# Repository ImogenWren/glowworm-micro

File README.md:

# glowworm-micro

Project to build a small battery powered handheld lighting controller for creative macro photography

## Project Due Data: 25/12/25

## Desired Features
- Arduino IoT33 Controller (could be ported to ESP32)
- 1S Lipo battery pack with charger
- Power on and off device using external interrupts
- Rotary Encoder for changing values

- Buttons to select parameter
- Detachable WS2821 Led Strip with 3D printed diffuser options
- 3D printed & ergonomic case
- fastLED library

- 2 Channel Lighting, each channel will have independent
    - Hue
    - Saturation
    - Brightness

Additional control ->  blend mode
- Unblended -> Colours remain seperate
- Direct Blend ->  blend will mix colours directly  
- Colour wheel short blend -> two channels will blend via the shortest route around the colour wheel between them
- colour wheel long blend -> two channels will blend via the longest path around the colour wheel

## Strech Goals
- Save & Recall current settings on shutdown/powerup
- OLED screen displaying all parameters
- highlight currently selected parameter
- Battery indicator
- PCB for control system
- PCB for LED Strip
- Advanced colour palettes

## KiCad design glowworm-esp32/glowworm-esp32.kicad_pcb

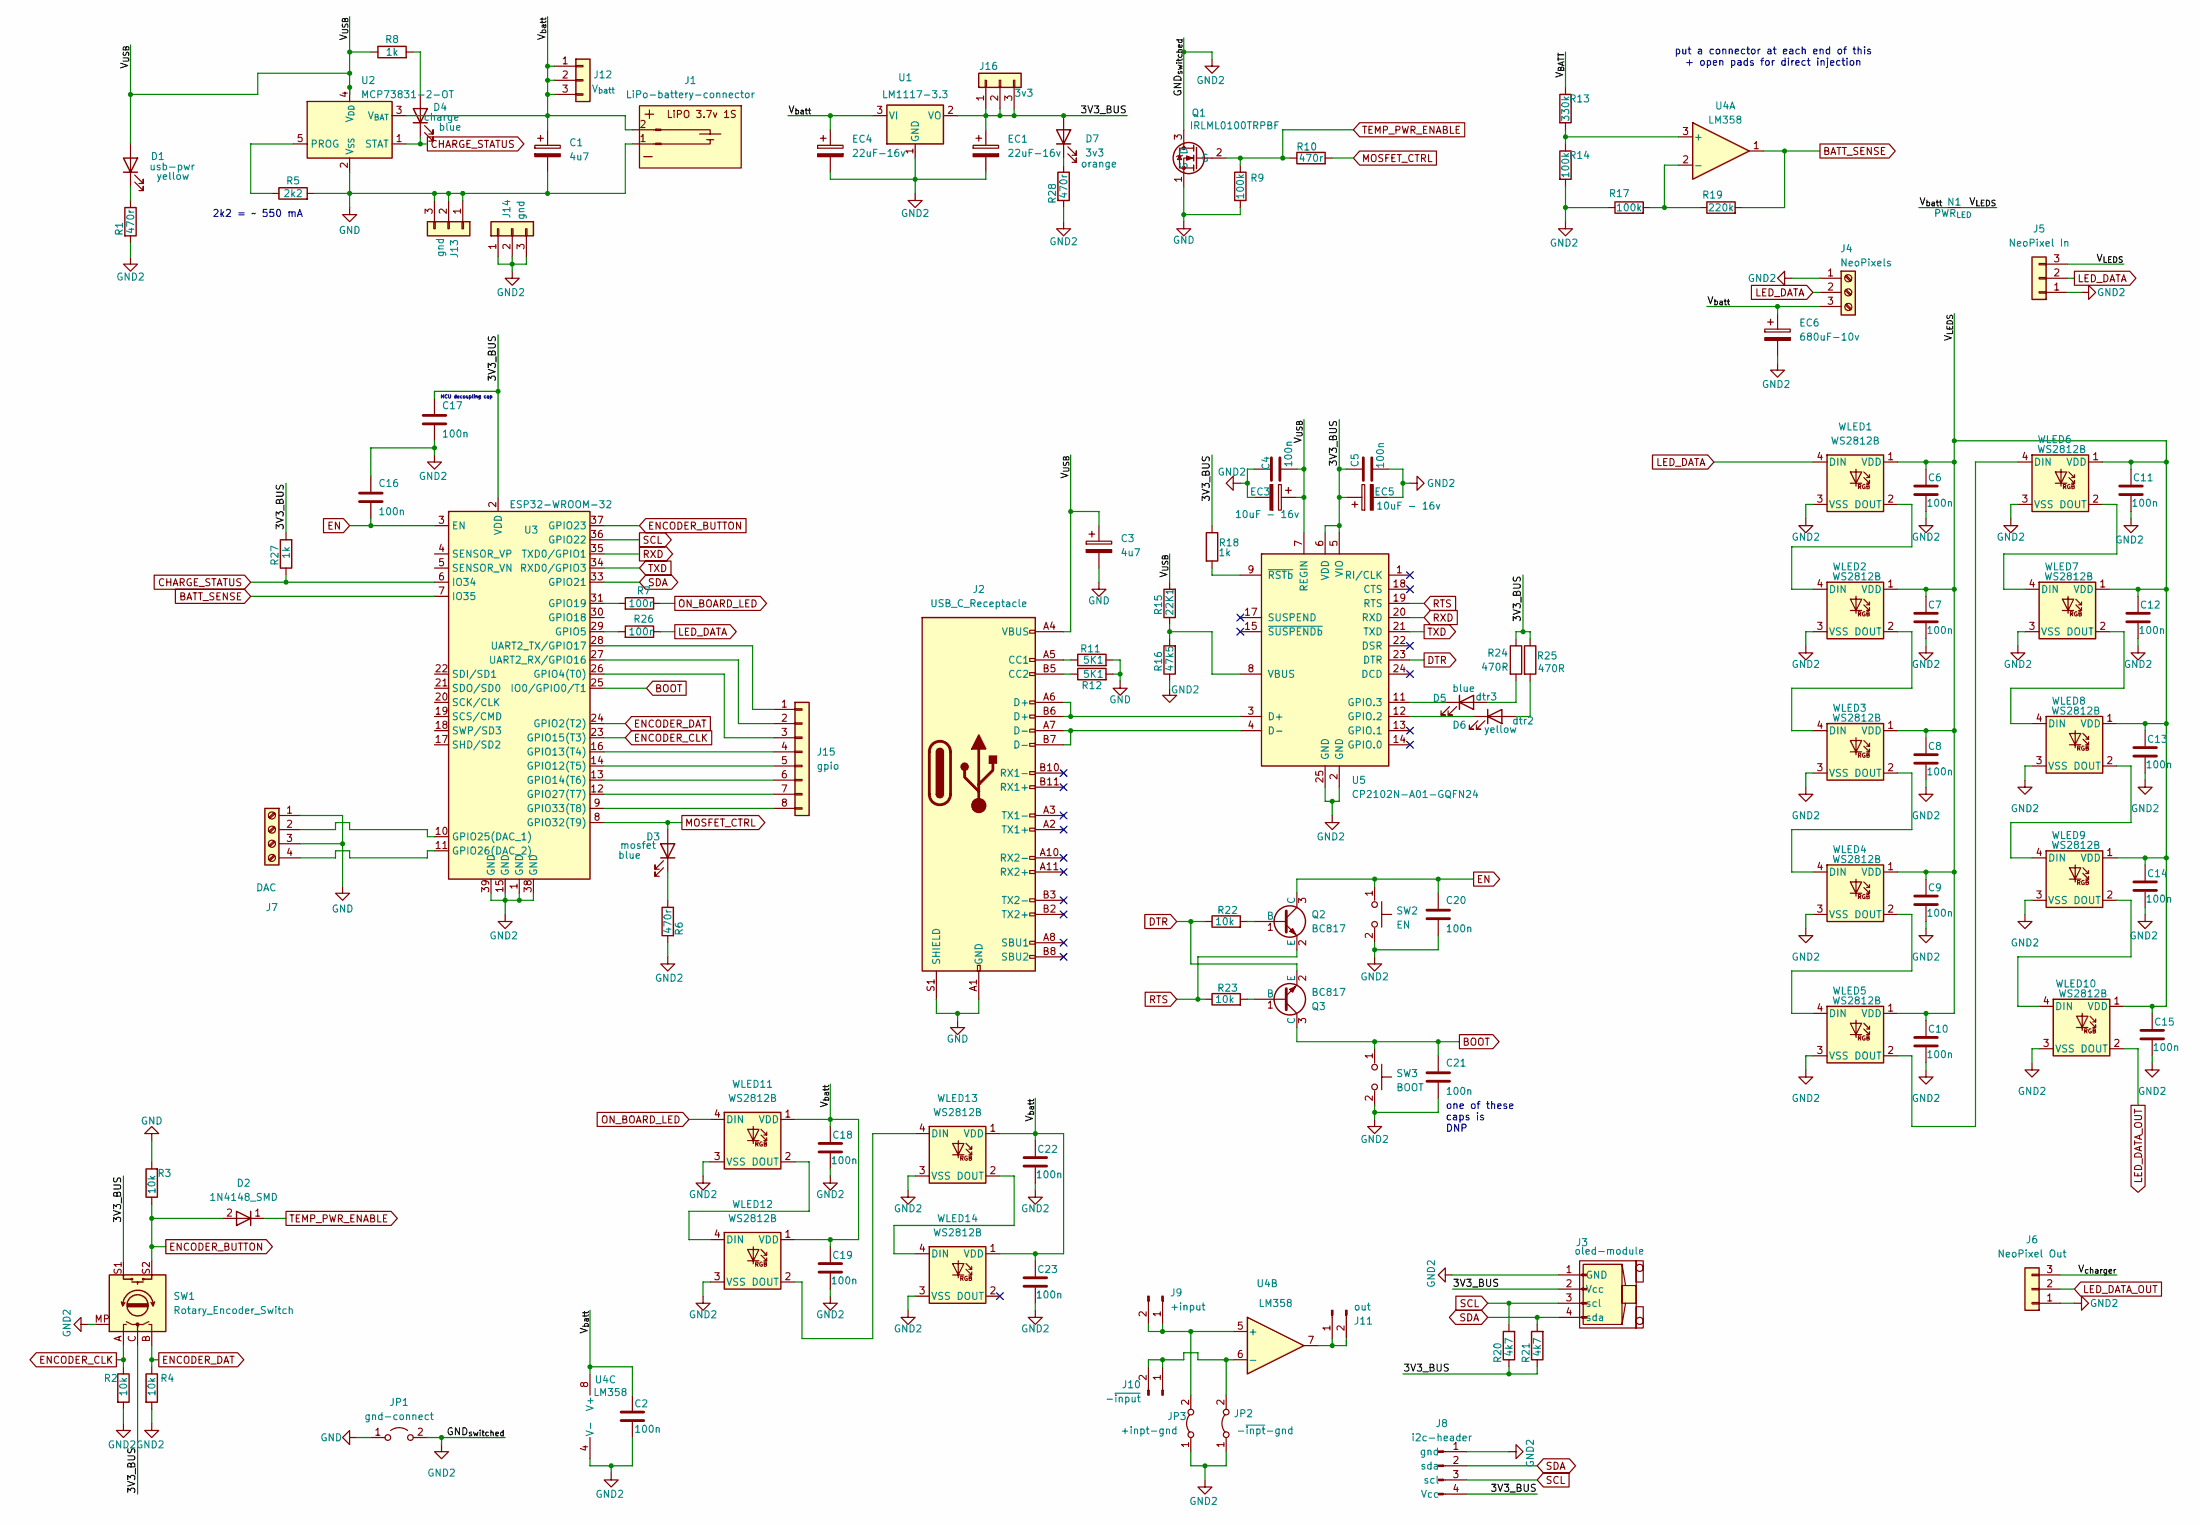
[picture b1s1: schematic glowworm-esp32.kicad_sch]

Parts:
C1, C3: 4u7; CP_EIA-2012-12_Kemet-R_Pad1.30x1.05mm_HandSolder; JLCpart C1954175
C2, C4, C5, C6, C7, C8, C9, C10, C11, C12, C13, C14, C15, C16, C17, C18, C19, C20, C21, C22, C23: 100n; C_0603_1608Metric_Pad1.08x0.95mm_HandSolder; JLCpart C779975
D1: usb-pwr; D_0603_1608Metric_Pad1.05x0.95mm_HandSolder; JLCpart C84261
D2: 1N4148_SMD; D_MiniMELF_kawaii
D3: mosfet; D_0603_1608Metric_Pad1.05x0.95mm_HandSolder; JLCpart C84259
D4: charge; D_0603_1608Metric_Pad1.05x0.95mm_HandSolder; JLCpart C84259
D5: dtr3; D_0603_1608Metric_Pad1.05x0.95mm_HandSolder; JLCpart C84259
D6: dtr2; D_0603_1608Metric_Pad1.05x0.95mm_HandSolder; JLCpart C84261
D7: 3v3; D_0805_2012Metric_Pad1.15x1.40mm_HandSolder
EC1, EC4: 22uF-16v; CP_Elec_4x5.4; JLCpart C3356
EC3, EC5: 10uF - 16v; CP_Elec_4x5.4; JLCpart C3357
EC6: 680uF-10v; CP_Elec_10x10; JLCpart C225872
J1: LiPo-battery-connector; Molex_KK-254_AE-6410-02A_1x02_P2.54mm_Vertical_copy
J2: USB_C_Receptacle; USB_C_Receptacle_GCT_USB4105-xx-A_16P_TopMnt_Horizontal; JLCpart C134092
J3: oled-module; oled-screen-i2c
J4: NeoPixels; TerminalBlock_01_03_medium_5.008mm
J5: NeoPixel In; PinHeader_1x03_P2.54mm_Vertical
J6: NeoPixel Out; PinHeader_1x03_P2.54mm_Vertical
J7: DAC; TerminalBlock_Phoenix_MPT-0,5-4-2.54_1x04_P2.54mm_Horizontal
J8: i2c-header; i2c-pin-header-A
J9: +input; PinHeader_1x02_P2.54mm_Vertical
J10: -~{input}; PinHeader_1x02_P2.54mm_Vertical
J11: out; PinHeader_1x02_P2.54mm_Vertical
J12: V_{batt}; PinHeader_1x03_P2.54mm_Vertical
J13, J14: gnd; PinHeader_1x03_P2.54mm_Vertical
J15: gpio; PinHeader_1x08_P2.54mm_Vertical
J16: 3v3; PinHeader_1x03_P2.54mm_Vertical
JP1: gnd-connect; SolderJumper-2_P1.3mm_Open_RoundedPad1.0x1.5mm
JP2: -~{inpt}-gnd; SolderJumper-2_P1.3mm_Bridged_RoundedPad1.0x1.5mm
JP3: +inpt-gnd; SolderJumper-2_P1.3mm_Bridged_RoundedPad1.0x1.5mm
N1: PWR_{LED}; NetTie-2_SMD_Pad0.5mm
Q1: IRLML0100TRPBF; SOT-23
Q2, Q3: BC817; SOT-23; JLCpart C2137
R1, R6, R10, R28: 470r; R_0603_1608Metric_Pad0.98x0.95mm_HandSolder
R2, R3, R4, R22, R23: 10k; R_0603_1608Metric_Pad0.98x0.95mm_HandSolder
R5: 2k2; R_0603_1608Metric_Pad0.98x0.95mm_HandSolder
R7, R26: 100r; R_0603_1608Metric_Pad0.98x0.95mm_HandSolder
R8, R18, R27: 1k; R_0603_1608Metric_Pad0.98x0.95mm_HandSolder
R9, R14, R17: 100k; R_0603_1608Metric_Pad0.98x0.95mm_HandSolder
R11, R12: 5K1; R_0603_1608Metric_Pad0.98x0.95mm_HandSolder
R13: 330k; R_0603_1608Metric_Pad0.98x0.95mm_HandSolder
R15: 22K1; R_0603_1608Metric_Pad0.98x0.95mm_HandSolder
R16: 47k5; R_0603_1608Metric_Pad0.98x0.95mm_HandSolder
R19: 220k; R_0603_1608Metric_Pad0.98x0.95mm_HandSolder
R20, R21: 4k7; R_0603_1608Metric_Pad0.98x0.95mm_HandSolder
R24, R25: 470R; R_0603_1608Metric_Pad0.98x0.95mm_HandSolder
SW1: Rotary_Encoder_Switch; RotaryEncoder_Alps_EC12E-Switch_Vertical_H20mm
SW2: EN; SW_SPST_EVQPE1; JLCpart C699451
SW3: BOOT; SW_SPST_EVQPE1; JLCpart C699451
U1: LM1117-3.3; SOT-223-3_TabPin2_1
U2: MCP73831-2-OT; SOT-23-5; JLCpart C424093
U3: ESP32-WROOM-32; JLCpart C473012 - C529577
U4: LM358; SOIC-8_3.9x4.9mm_P1.27mm
U5: CP2102N-A01-GQFN24; QFN-24-1EP_4x4mm_P0.5mm_EP2.6x2.6mm
WLED1, WLED2, WLED3, WLED4, WLED5, WLED6, WLED7, WLED8, WLED9, WLED10, WLED11, WLED12, WLED13, WLED14: WS2812B; LED_WS2812B_PLCC4_5.0x5.0mm_P3.2mm; JLCpart C2920042

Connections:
/3V3_BUS: C5.1, C17.1, D7.2 (A), EC1.1, EC5.1, J3.2 (Vcc), J8.4 (Vcc), J16.1, J16.2, J16.3, R18.1, R20.1, R21.1, R24.1, R25.1, R27.2, SW1.C, SW1.S1, U1.2 (VO), U3.2 (VDD), U5.5 (VIO), U5.6 (VDD)
/V_{BATT}: R13.1
/V_{LEDS}: C6.1, C7.1, C8.1, C9.1, C10.1, C11.1, C12.1, C13.1, C14.1, C15.1, J5.3, N1.2 (C), WLED1.1 (VDD), WLED2.1 (VDD), WLED3.1 (VDD), WLED4.1 (VDD), WLED5.1 (VDD), WLED6.1 (VDD), WLED7.1 (VDD), WLED8.1 (VDD), WLED9.1 (VDD), WLED10.1 (VDD)
/V_{USB}: C3.1, C4.2, D1.2 (A), EC3.1, J2.A4 (VBUS), J2.A9 (VBUS), J2.B4 (VBUS), J2.B9 (VBUS), R8.1, R15.2, U2.4 (V_{DD}), U5.7 (REGIN)
/V_{batt}: C1.1, C2.1, C18.1, C19.1, C22.1, C23.1, EC4.1, EC6.1, J1.2, J4.3 (Pin_1), J12.1, J12.2, J12.3, N1.1 (A), U1.3 (VI), U2.3 (V_{BAT}), U4.8 (V+), WLED11.1 (VDD), WLED12.1 (VDD), WLED13.1 (VDD), WLED14.1 (VDD)
/V_{charger}: J6.3
BATT_SENSE: R19.2, U3.7 (IO35), U4.1
BOOT: C21.1, Q3.3 (C), SW3.1, U3.25 (IO0/GPIO0/T1)
CHARGE_STATUS: D4.1 (K), R27.1, U2.1 (STAT), U3.6 (IO34)
DTR: Q3.2 (E), R22.1, U5.23 (DTR)
EN: C16.2, C20.1, Q2.3 (C), SW2.1, U3.3 (EN)
ENCODER_BUTTON: D2.2 (A), R3.1, SW1.S2, U3.37 (GPIO23)
ENCODER_CLK: R2.1, SW1.A, U3.23 (GPIO15(T3))
ENCODER_DAT: R4.1, SW1.B, U3.24 (GPIO2(T2))
GND: C1.2, C3.2, J1.1, J2.A1 (GND), J2.A12 (GND), J2.B1 (GND), J2.B12 (GND), J2.S1 (SHIELD), J7.1, J7.3, J13.1, J13.2, J13.3, JP1.1 (A), Q1.1 (S), R3.2, R5.2, R9.2, R11.2, R12.2, U2.2 (V_{SS})
GND2: C2.2, C4.1, C5.2, C6.2, C7.2, C8.2, C9.2, C10.2, C11.2, C12.2, C13.2, C14.2, C15.2, C16.1, C17.2, C18.2, C19.2, C20.2, C21.2, C22.2, C23.2, EC1.2, EC3.2, EC4.2, EC5.2, EC6.2, J3.1 (GND), J4.1, J5.1, J6.1, J8.1 (gnd), J14.1, J14.2, J14.3, JP1.2 (B), JP2.1 (A), JP3.1 (A), Q1.3 (D), R1.2, R2.2, R4.2, R6.2, R14.2, R16.1, R17.1, R28.2, SW1.MP, SW2.2, SW3.2, U1.1 (GND), U3.1 (GND), U3.15 (GND), U3.38 (GND), U3.39 (GND), U4.4 (V-), U5.2 (GND), U5.25 (GND), WLED1.3 (VSS), WLED2.3 (VSS), WLED3.3 (VSS), WLED4.3 (VSS), WLED5.3 (VSS), WLED6.3 (VSS), WLED7.3 (VSS), WLED8.3 (VSS), WLED9.3 (VSS), WLED10.3 (VSS), WLED11.3 (VSS), WLED12.3 (VSS), WLED13.3 (VSS), WLED14.3 (VSS)
LED_DATA: J4.2, J5.2, R26.1, WLED1.4 (DIN)
LED_DATA_OUT: J6.2, WLED10.2 (DOUT)
MOSFET_CTRL: D3.2 (A), R10.2, U3.8 (GPIO32(T9))
unnamed: D1.1 (K), R1.1
unnamed: D3.1 (K), R6.1
unnamed: D4.2 (A), R8.2
unnamed: D5.2 (A), R24.2
unnamed: D5.1 (K), U5.11 (GPIO.3)
unnamed: D6.2 (A), R25.2
unnamed: D6.1 (K), U5.12 (GPIO.2)
unnamed: D7.1 (K), R28.1
unnamed: J2.A5 (CC1), R11.1
unnamed: J2.B5 (CC2), R12.1
unnamed: J7.2, U3.10 (GPIO25(DAC_1))
unnamed: J7.4, U3.11 (GPIO26(DAC_2))
unnamed: J9.1, J9.2, JP3.2 (B), U4.5 (+)
unnamed: J10.1, J10.2, JP2.2 (B), U4.6 (-)
unnamed: J11.1, J11.2, U4.7
unnamed: J15.1, U3.28 (UART2_TX/GPIO17)
unnamed: J15.2, U3.27 (UART2_RX/GPIO16)
unnamed: J15.3, U3.26 (GPIO4(T0))
unnamed: J15.4, U3.16 (GPIO13(T4))
unnamed: J15.5, U3.14 (GPIO12(T5))
unnamed: J15.6, U3.13 (GPIO14(T6))
unnamed: J15.7, U3.12 (GPIO27(T7))
unnamed: J15.8, U3.9 (GPIO33(T8))
unnamed: Q2.1 (B), R22.2
unnamed: Q3.1 (B), R23.2
unnamed: R5.1, U2.5 (PROG)
unnamed: R26.2, U3.29 (GPIO5)
unnamed: R7.2, U3.31 (GPIO19)
unnamed: R13.2, R14.1, U4.3 (+)
unnamed: R17.2, R19.1, U4.2 (-)
unnamed: J2.A6 (D+), J2.B6 (D+), U5.3 (D+)
unnamed: J2.A7 (D-), J2.B7 (D-), U5.4 (D-)
unnamed: R15.1, R16.2, U5.8 (VBUS)
unnamed: R18.2, U5.9 (~RSTb)
unnamed: WLED1.2 (DOUT), WLED2.4 (DIN)
unnamed: WLED2.2 (DOUT), WLED3.4 (DIN)
unnamed: WLED3.2 (DOUT), WLED4.4 (DIN)
unnamed: WLED4.2 (DOUT), WLED5.4 (DIN)
unnamed: WLED5.2 (DOUT), WLED6.4 (DIN)
unnamed: WLED6.2 (DOUT), WLED7.4 (DIN)
unnamed: WLED7.2 (DOUT), WLED8.4 (DIN)
unnamed: WLED8.2 (DOUT), WLED9.4 (DIN)
unnamed: WLED9.2 (DOUT), WLED10.4 (DIN)
unnamed: WLED11.2 (DOUT), WLED12.4 (DIN)
unnamed: WLED12.2 (DOUT), WLED13.4 (DIN)
unnamed: WLED13.2 (DOUT), WLED14.4 (DIN)
ON_BOARD_LED: R7.1, WLED11.4 (DIN)
RTS: Q2.2 (E), R23.1, U5.19 (RTS)
RXD: U3.35 (TXD0/GPIO1), U5.20 (RXD)
SCL: J3.3 (scl), J8.3 (scl), R20.2, U3.36 (GPIO22)
SDA: J3.4 (sda), J8.2 (sda), R21.2, U3.33 (GPIO21)
TEMP_PWR_ENABLE: D2.1 (K), Q1.2 (G), R9.1, R10.1
TXD: U3.34 (RXD0/GPIO3), U5.21 (TXD)

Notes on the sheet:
put a connector at each end of this + open pads for direct injection
MCU decoupling cap
one of these caps is DNP
2k2 = ~ 550 mA

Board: 2 copper layers, 108 parts (0 on the bottom side), 70 nets, no tracks yet.

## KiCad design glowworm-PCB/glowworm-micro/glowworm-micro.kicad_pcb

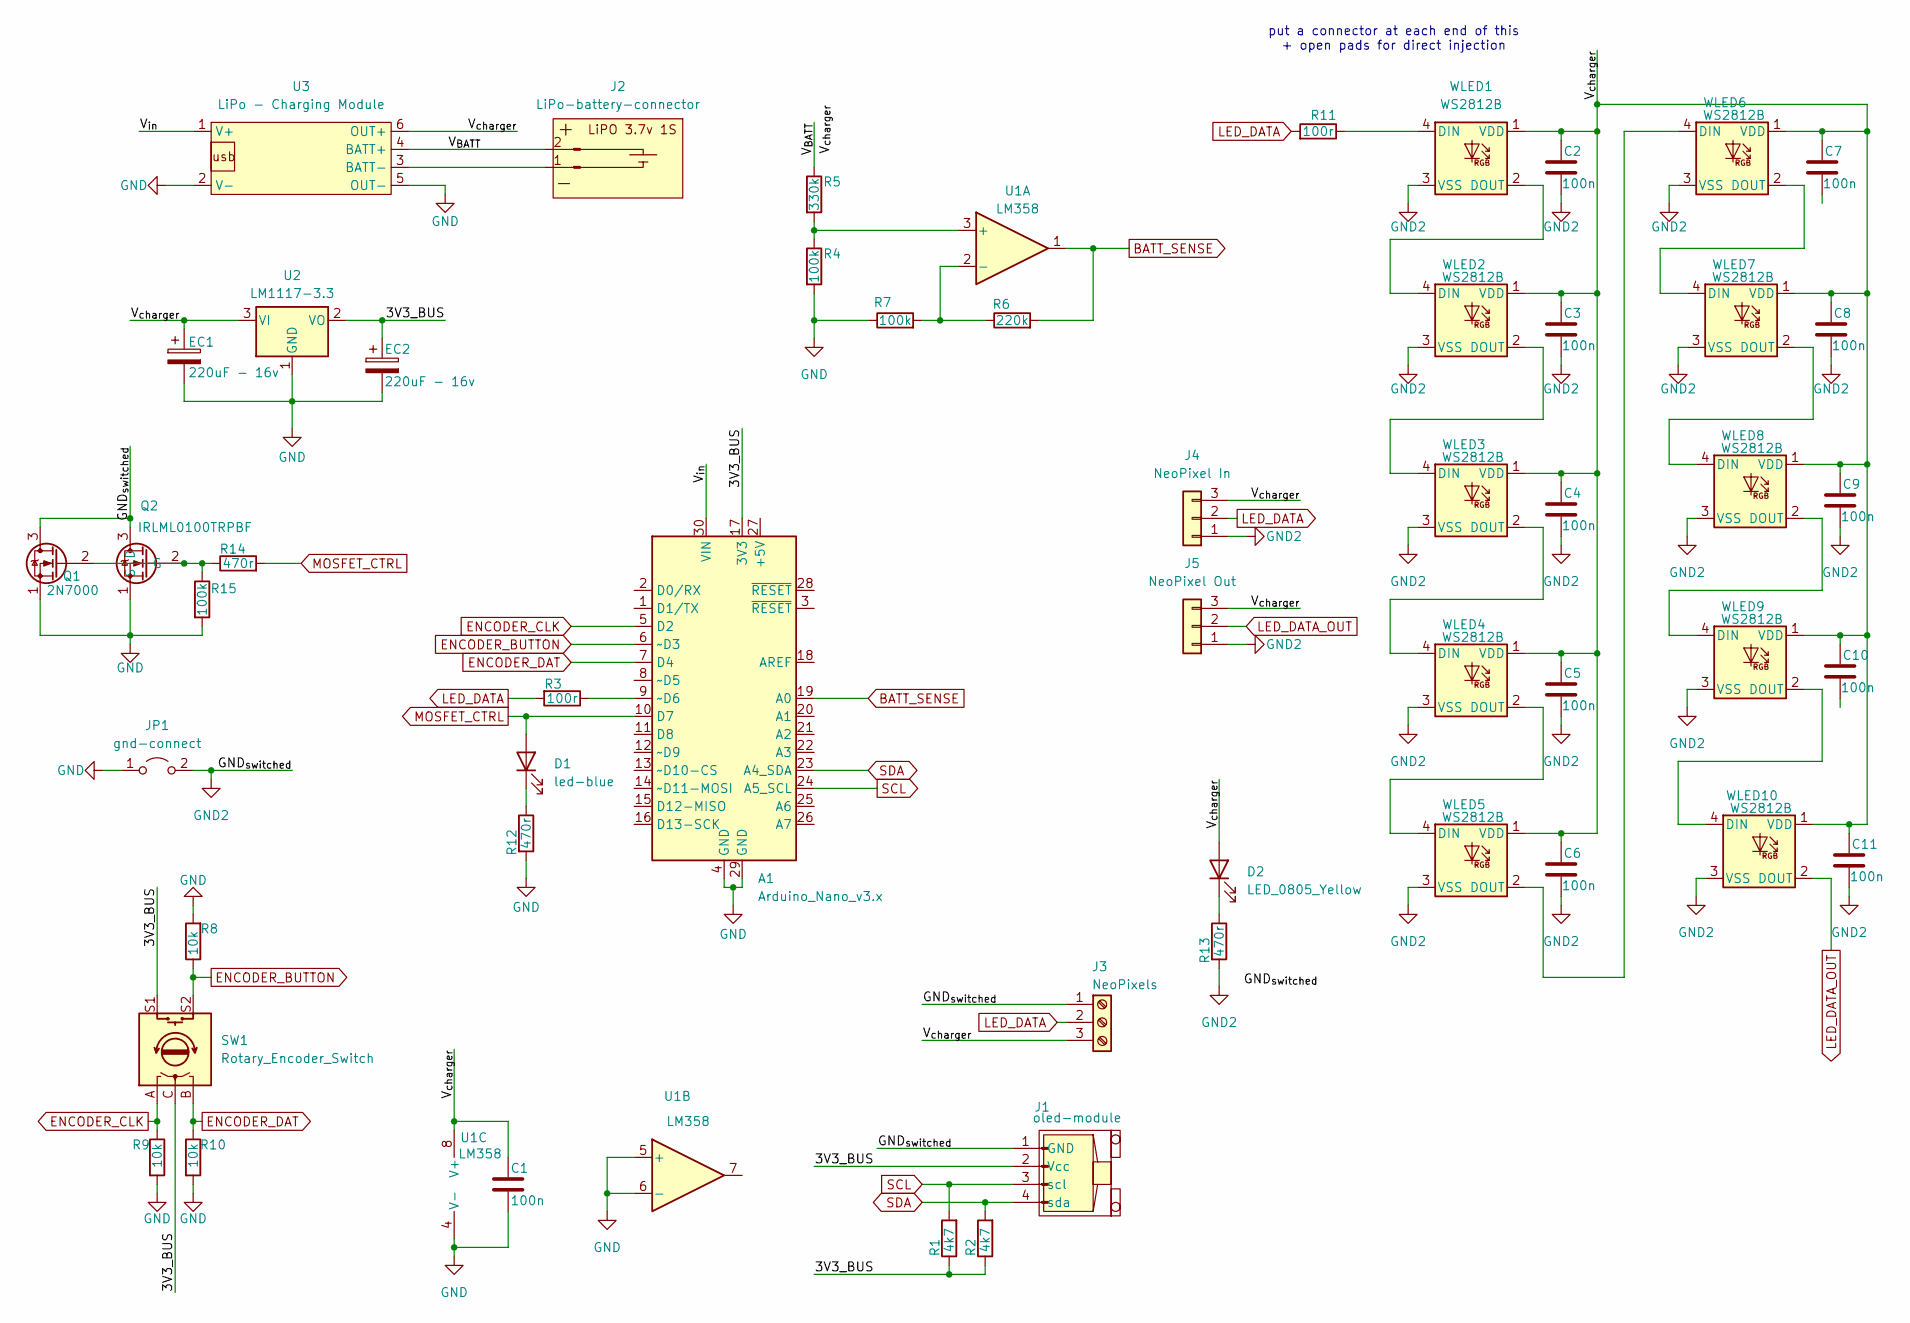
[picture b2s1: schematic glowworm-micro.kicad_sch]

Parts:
A1: Arduino_Nano_v3.x; Arduino_Nano
C1, C2, C3, C4, C5, C6, C7, C8, C9, C10, C11: 100n; C_0603_1608Metric_Pad1.08x0.95mm_HandSolder; JLCpart C779975
D1: led-blue; D_0805_2012Metric_Pad1.15x1.40mm_HandSolder; JLCpart C84259
D2: LED_0805_Yellow; D_0805_2012Metric_Pad1.15x1.40mm_HandSolder; JLCpart C84261
EC1, EC2: 220uF - 16v; CP_Elec_6.3x7.7; JLCpart C4747974
J1: oled-module; oled-screen-i2c
J2: LiPo-battery-connector; Molex_KK-254_AE-6410-02A_1x02_P2.54mm_Vertical_copy
J3: NeoPixels; TerminalBlock_01_03_medium_5.008mm
J4: NeoPixel In; PinHeader_1x03_P2.54mm_Vertical
J5: NeoPixel Out; PinHeader_1x03_P2.54mm_Vertical
JP1: gnd-connect; SolderJumper-2_P1.3mm_Open_RoundedPad1.0x1.5mm
Q1: 2N7000; TO-92_Inline
Q2: IRLML0100TRPBF; SOT-23
R1, R2: 4k7; R_0603_1608Metric_Pad0.98x0.95mm_HandSolder
R3, R11: 100r; R_0603_1608Metric_Pad0.98x0.95mm_HandSolder
R4, R7, R15: 100k; R_0603_1608Metric_Pad0.98x0.95mm_HandSolder
R5: 330k; R_0603_1608Metric_Pad0.98x0.95mm_HandSolder
R6: 220k; R_0603_1608Metric_Pad0.98x0.95mm_HandSolder
R8, R9, R10: 10k; R_0603_1608Metric_Pad0.98x0.95mm_HandSolder
R12, R13, R14: 470r; R_0603_1608Metric_Pad0.98x0.95mm_HandSolder
SW1: Rotary_Encoder_Switch; RotaryEncoder_Alps_EC12E-Switch_Vertical_H20mm
U1: LM358; SOIC-8_3.9x4.9mm_P1.27mm
U2: LM1117-3.3; SOT-223-3_TabPin2_1
U3: LiPo - Charging Module; lipo-charging-module
WLED1, WLED2, WLED3, WLED4, WLED5, WLED6, WLED7, WLED8, WLED9, WLED10: WS2812B; LED_WS2812B_PLCC4_5.0x5.0mm_P3.2mm; JLCpart C2920042

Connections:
/3V3_BUS: A1.17 (3V3), EC2.1, J1.2 (Vcc), R1.1, R2.1, SW1.C, SW1.S1, U2.2 (VO)
/V_{BATT}: J2.2, R5.1, U3.4 (BATT+)
/V_{charger}: C1.1, C2.1, C3.1, C4.1, C5.1, C6.1, C7.1, C8.1, C9.1, C10.1, C11.1, D2.2 (A), EC1.1, J3.3 (Pin_1), J4.3, J5.3, U1.8 (V+), U2.3 (VI), U3.6 (OUT+), WLED1.1 (VDD), WLED2.1 (VDD), WLED3.1 (VDD), WLED4.1 (VDD), WLED5.1 (VDD), WLED6.1 (VDD), WLED7.1 (VDD), WLED8.1 (VDD), WLED9.1 (VDD), WLED10.1 (VDD)
/V_{in}: A1.30 (VIN), U3.1 (V+)
BATT_SENSE: A1.19 (A0), R6.2, U1.1
ENCODER_BUTTON: A1.6 (~D3), R8.1, SW1.S2
ENCODER_CLK: A1.5 (D2), R9.1, SW1.A
ENCODER_DAT: A1.7 (D4), R10.1, SW1.B
GND: A1.4 (GND), A1.29 (GND), C1.2, EC1.2, EC2.2, JP1.1 (A), Q1.1 (S), Q2.1 (S), R4.2, R7.1, R8.2, R9.2, R10.2, R12.2, R15.2, U1.4 (V-), U1.5 (+), U1.6 (-), U2.1 (GND), U3.2 (V-), U3.5 (OUT-)
GND2: C2.2, C3.2, C4.2, C5.2, C6.2, C8.2, C9.2, C11.2, J1.1 (GND), J3.1, J4.1, J5.1, JP1.2 (B), Q1.3 (D), Q2.3 (D), R13.2, WLED1.3 (VSS), WLED2.3 (VSS), WLED3.3 (VSS), WLED4.3 (VSS), WLED5.3 (VSS), WLED6.3 (VSS), WLED7.3 (VSS), WLED8.3 (VSS), WLED9.3 (VSS), WLED10.3 (VSS)
LED_DATA: J3.2, J4.2, R3.2, R11.2
LED_DATA_OUT: J5.2, WLED10.2 (DOUT)
MOSFET_CTRL: A1.10 (D7), D1.2 (A), R14.2
unnamed: A1.9 (~D6), R3.1
unnamed: D1.1 (K), R12.1
unnamed: D2.1 (K), R13.1
unnamed: J2.1, U3.3 (BATT-)
unnamed: Q1.2 (G), Q2.2 (G), R14.1, R15.1
unnamed: R4.1, R5.2, U1.3 (+)
unnamed: R6.1, R7.2, U1.2 (-)
unnamed: R11.1, WLED1.4 (DIN)
unnamed: WLED1.2 (DOUT), WLED2.4 (DIN)
unnamed: WLED2.2 (DOUT), WLED3.4 (DIN)
unnamed: WLED3.2 (DOUT), WLED4.4 (DIN)
unnamed: WLED4.2 (DOUT), WLED5.4 (DIN)
unnamed: WLED5.2 (DOUT), WLED6.4 (DIN)
unnamed: WLED6.2 (DOUT), WLED7.4 (DIN)
unnamed: WLED7.2 (DOUT), WLED8.4 (DIN)
unnamed: WLED8.2 (DOUT), WLED9.4 (DIN)
unnamed: WLED9.2 (DOUT), WLED10.4 (DIN)
SCL: A1.24 (A5_SCL), J1.3 (scl), R1.2
SDA: A1.23 (A4_SDA), J1.4 (sda), R2.2

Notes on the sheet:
put a connector at each end of this + open pads for direct injection

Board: 2 copper layers, 49 parts (0 on the bottom side), 31 nets, no tracks yet.

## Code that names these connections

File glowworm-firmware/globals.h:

#pragma once

#ifndef globals_h
#define globals_h




// External Libraries
#include <SPI.h>
#include <Wire.h>
#include <Adafruit_GFX.h>
#include <Adafruit_SSD1306.h>
#include <FastLED.h>
#include <ledObject.h>
#include <buttonObject.h>
//#include <multiMeter.h>
#include "calibration.h"

#include <ledObject.h>
#include <buttonObject.h>

const int BUTTON_PIN = 23;
const int MOSFET_PIN = 32;

const int GREEN_LED_PIN = 5;
const int RED_LED_PIN = 19;


//#include <Fonts/FreeMonoBold12pt7b.h >
//#include <Fonts/FreeSansBold12pt7b.h >
//#include <Fonts/FreeSansBold9pt7b.h >

//#include <avr/dtostrf.h>  //needed for SAMD21 only


// Configuration
#define SHOW_SPASH_SCREEN true

// IO PINS
// I2C
#define SDA_PIN A4
#define SCL_PIN A5
// Encoder
#define ENCODER_CLK 2
#define ENCODER_DAT 4
// smart LEDS
#define LED_DATA_PIN 14//6
// sleep function vars
#define ENCODER_BUTTON_EXTINT8 3
#define MOSFET_CTRL 7

// Battery Monitor
#define BATTERY_SENSE_PIN A0
//#define INPUT_V_MAX 3.3      // Max Voltage for the ADC Input Pin
//#define ADC_RESOLUTION 10  // Typically 10bit on Arduino Platforms
//#define DO_TABLE_CAL false

#define DIRECTION_CW 1    // clockwise direction
#define DIRECTION_CCW -1  // counter-clockwise direction

#define ENCODER_PPR 600
#define ENCODER_TYPE TWO_WIRE
#define ENCODER_NAME "encoder"

// Button


// LED


#define NUM_LEDS 6
#define START_BRIGHTNESS 200
#define LED_TYPE WS2811
#define COLOR_ORDER GRB
#define UPDATES_PER_SECOND 100
#define MAX_LED_LENGTH 255

//CRGB leds[NUM_LEDS];
CRGB leds[MAX_LED_LENGTH];  // set this for the maximum suitable string, and will only be limited in runtime via user setting ( default 8)





//ledObject indicator(LED_BUILTIN);


//#include <ArduinoLowPower.h>
#define WAKE_UP_TIME 2500

volatile bool wokeFromInterrupt = false;
volatile bool sleep_active = false;

bool sleep_block = false;
unsigned long wake_start;




// ADC Consts
#define CURRENT_ADC_OFFSET 0  //-323
#define CURRENT_I_OFFSET -5

// Timing Consts



// Global Objects
buttonObject button(ENCODER_BUTTON_EXTINT8, BUTTON_PULL_HIGH);
ledObject indicator(LED_BUILTIN);
//multiMeter voltMeter(BATTERY_SENSE_PIN, METER_TYPE, INPUT_V_MAX, ADC_RESOLUTION, DO_TABLE_CAL);
calibration cal;

// OLED
#define SCREEN_WIDTH 128  // OLED display width, in pixels
#define SCREEN_HEIGHT 64  // OLED display height, in pixels

#define OLED_ADDR 0x3C
Adafruit_SSD1306 display(SCREEN_WIDTH, SCREEN_HEIGHT, &Wire, -1);

#if (SSD1306_LCDHEIGHT != 64)
//#error("Height incorrect, please fix Adafruit_SSD1306.h!");
#endif

#include "sleepFunctions.h"

volatile uint8_t encoderVal = 0;
uint8_t buttonPressed = 0;
volatile int direction = DIRECTION_CW;
volatile uint32_t last_time;
volatile bool ISR_triggered = false;

// Consts
//const char SYSTEM_NAME = {"Practable Power Hat V1.0"}
const uint8_t I2C_ADDRESS = 0x08;  // Address of i2c slave (self)

uint8_t active_stat = 0;  // The active high bit highlights the selected sat in the UI
bool select_mode = true;  // when select mode is active, encoder used to select active stat. When false,
// encoder changes value of active stat
bool updateLEDs = true;
uint8_t multi_update = 0;
bool num_leds_updated = true;

// LED data struc -> set up like this to make saving and recalling data from memory easy

// blend modes
typedef enum {
  NO_BLEND,
  DIRECT_BLEND,
  WHEEL_SHORT,
  WHEEL_LONG
} blend_mode;

//blend_mode currentBlend = NO_BLEND;

static char blendNames[][8] = {
  "None",
  "Direct",
  "Short",
  "Long"
};



struct LED_data {  // Channel A
  uint8_t ch_A_hue;
  uint8_t ch_A_sat;
  uint8_t ch_A_bright;
  uint8_t ch_B_hue;
  uint8_t ch_B_sat;
  uint8_t ch_B_bright;
  int8_t blend;
  uint8_t num_leds;
};

LED_data defaultData = {
  100, 255, START_BRIGHTNESS,
  200, 255, START_BRIGHTNESS,
  DIRECT_BLEND, NUM_LEDS
};

LED_data currentLED = defaultData;


// palette blending options
CRGBPalette16 outputPalette;
TBlendType currentBlending = LINEARBLEND_NOWRAP;

CHSV colourA = CHSV(40, 255, 255);
CHSV colourB = CHSV(128, 255, 255);
// Channel A
/*
uint8_t ch_A_hue = 20;
uint8_t ch_A_sat = 255;
uint8_t ch_A_bright = START_BRIGHTNESS;

// Channel B
uint8_t ch_B_hue = 230;
uint8_t ch_B_sat = 255;
uint8_t ch_B_bright = START_BRIGHTNESS;
*/

// All Channels
//uint8_t blend = 0;
//uint8_t num_leds = 6;

#define BATTERY_SAMPLES_REQ 20
uint8_t battery_indicator_level = 0;  // while charging this can cylce from 1 to 3
uint8_t batt_indicator_unsmoothed[BATTERY_SAMPLES_REQ + 2];
uint8_t battery_samples_taken = 0;
int16_t battery_adc = 0;
float batteryVoltage;

// Internal Headers
#include "encoder.h"
#include "batteryMonitor.h"
#include "oled.h"
#include "leds.h"
#include "state_machines.h"
#include "power_sense.h"


#endif

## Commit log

2025-12-05 Update README with project details and features
    Added project due date and detailed desired features.
2025-12-06 Revise project description and due date
    Updated project description and due date in README.
2025-12-06 Update README with image and formatting changes
    Added an image and improved formatting in the README.
2025-12-06 working on the logo because thats important
2025-12-07 working on firmware
2025-12-07 MVP hardware working
2025-12-07 Add image to README for project visualization
    Added an image to the README for visual reference.
2025-12-07 UI layout finished
2025-12-10 UI basically finished
2025-12-10 Direct blend using palettes implemented but slightly unpredictable
2025-12-12 Working on wake from interrupt example
2025-12-12 shutdown and power on test script is working
2025-12-12 shutdown working, ish, need to fix MOSFET power control hardware
2025-12-17 hardware prototype done
2025-12-17 battery monitor working
2025-12-20 lots of CAD work
2025-12-24 updated to case version 3
2026-01-01 working on battery monitor tuning
2026-02-26 ported to ESP32
2026-03-18 updates to pcb
